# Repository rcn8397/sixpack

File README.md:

# sixpack
Six-Pack Cherry MX Macro Pad

# Layout
Six Switch MX Layout

# Plate & Case

 * Switch Type: MX {_t:3}
 * Stabilizer Type: Cherry + Costar {_s:1}
 * Case Type: Sandwich
 * USB Cutout: On
   * Location: 0 (default)
   * Width: 12
 * Mount Holes: 4, 3, 8
 * Edge Padding: On, 10,10,10,10 (W,N,E,S)
 * Plate Corners: On, 4
 * Custom Polygons: Off
 * Kerf: Off
 * Key Unit Size: Off
 * Line Color: Off
 * Line Weight: Off

## 3D Printing
The plate and case are also hosted on [prusaprinters.org](https://www.prusaprinters.org/prints/113097-sixpack)

### Openscad
Each layer can be generated/customized using openscads customizer. 

### Slicing
I use Cura to slice, but I suspect any slicer will work. 

* Nozzle: 0.4mm
* Layer Height: 0.2mm
* Supports: No

# QMK
## Setup
## Compiling
Compile the code using QMK

     qmk compile -kb handwired/sixpack  -km default
     
## Flashing
Flash the target (ProMicro), note you must hit the reset switch to enter bootloader.

     qmk flash -kb handwired/sixpack  -km default
     
### Linux Issues
On Ubuntu 18.04 I needed to stop the ModemManger service to communicate with ttyACM0 serial device. 

    sudo systemctl stop ModemManager.service
    sudo systemctl disable ModemManager.service
    
 ## Customization
 TODO

# Resources
 * https://www.youtube.com/watch?v=IKe_hrvYH1M
 * http://www.keyboard-layout-editor.com/
 * http://builder.swillkb.com/
 * https://wiki.ai03.com/books/pcb-design/chapter/pcb-designer-guide
 * https://matt3o.com/hand-wiring-a-custom-keyboard/

## QMK
 * https://docs.qmk.fm/#/
 * https://docs.qmk.fm/#/hand_wire
 * Sixpack firmware (QMK forked) https://github.com/rcn8397/qmk_firmware/tree/personal/nordeen%2Fsixpack
 * Work flow https://docs.qmk.fm/#/newbs_git_using_your_master_branch

### QMK Git Workflow/Setup
Add the forked repo as a remote

      git remote add myfork git@github.com:rcn8397/qmk_firmware.git
      
Next verify the forked repo was added

      git remote -v
      
Should look something like:

      myfork	git@github.com:rcn8397/qmk_firmware.git (fetch)
      myfork	git@github.com:rcn8397/qmk_firmware.git (push)
      origin	https://github.com/qmk/qmk_firmware.git (fetch)
      origin	https://github.com/qmk/qmk_firmware.git (push)
      
Next push the development branch to the fork and track it.

      git push -u myfork

## Promicro
 * https://deskthority.net/wiki/Arduino_Pro_Micro#Pinout
 * https://golem.hu/guide/pro-micro-upgrade/
 * https://learn.sparkfun.com/tutorials/pro-micro--fio-v3-hookup-guide/troubleshooting-and-faq#ts-reset

## Atmega32u4 Data sheet

 * http://ww1.microchip.com/downloads/en/devicedoc/atmel-7766-8-bit-avr-atmega16u4-32u4_datasheet.pdf

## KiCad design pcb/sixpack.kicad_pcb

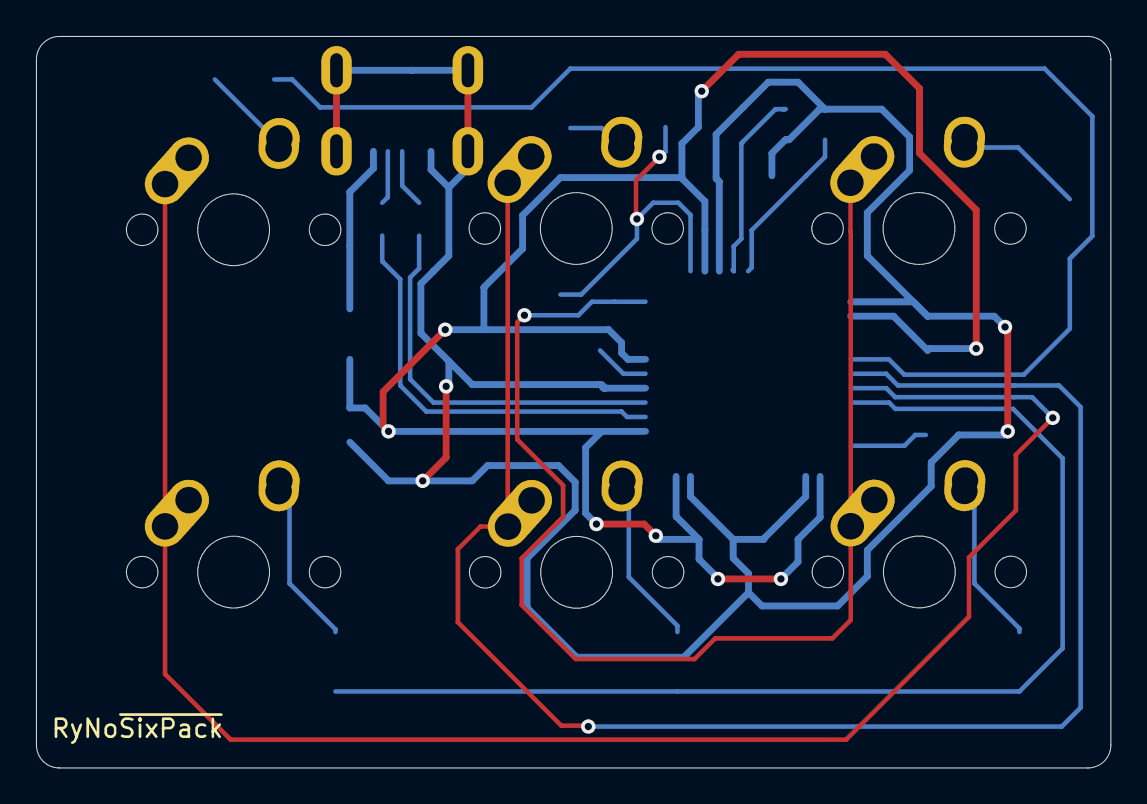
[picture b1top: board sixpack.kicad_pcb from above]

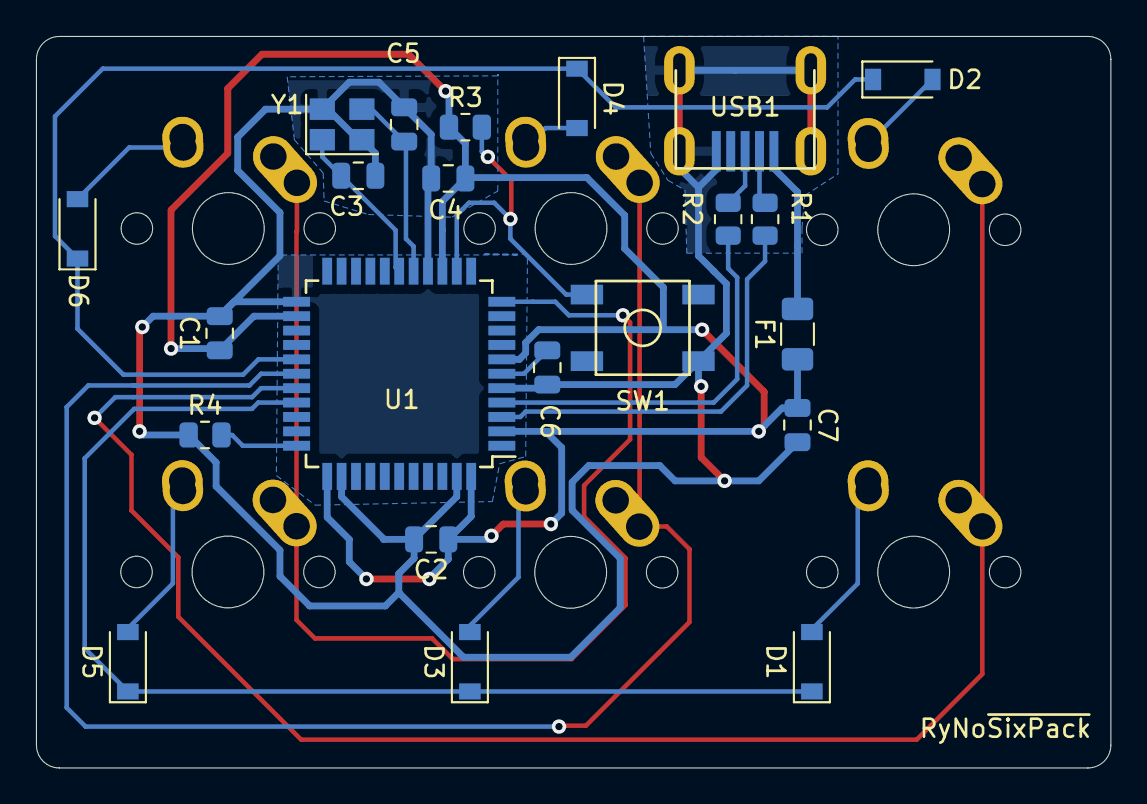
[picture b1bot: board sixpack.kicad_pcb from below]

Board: 2 copper layers, 59.7 x 40.6 mm, 28 parts (22 on the bottom side), 23 nets.

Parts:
C1, C2, C4: 0.1uF; C_0805_2012Metric
C3, C5: 22pF; C_0805_2012Metric
C6: 1uF; C_0805_2012Metric
C7: 10uF; C_0805_2012Metric
D1, D2, D3, D4, D5, D6: SOD-123; D_SOD-123
F1: 500mA; Fuse_1206_3216Metric
MX1, MX2, MX3, MX4, MX5, MX6: MX-NoLED; MX-1U-NoLED
R1, R2: 22; R_0805_2012Metric
R3, R4: 10k; R_0805_2012Metric
SW1: SW_Push; SKQG-1155865
U1: ATmega32U4-AU; TQFP-44_10x10mm_P0.8mm
USB1: Molex-0548190589
Y1: 16MHz; Crystal_SMD_3225-4Pin_3.2x2.5mm

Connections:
+5V: C1.1, C2.1, C4.1, C7.1, F1.1, R3.1, U1.2, U1.7, U1.14, U1.24, U1.34, U1.44
COL0: MX1.1, MX2.1, U1.29
COL1: MX3.1, MX4.1, U1.28
COL2: MX5.1, MX6.1, U1.11
D+: R2.2, USB1.3
D-: R1.2, USB1.4
GND: C1.2, C2.2, C3.2, C4.2, C5.2, C6.2, C7.2, R4.1, SW1.1, U1.5, U1.15, U1.23, U1.35, U1.43, USB1.1, USB1.6, Y1.2, Y1.4
unnamed: C3.1, U1.17, Y1.1
unnamed: C5.1, U1.16, Y1.3
unnamed: C6.1, U1.6
unnamed: D1.2, MX1.2
unnamed: D2.2, MX2.2
unnamed: D3.2, MX3.2
unnamed: D4.2, MX4.2
unnamed: D5.2, MX5.2
unnamed: D6.2, MX6.2
unnamed: R1.1, U1.3
unnamed: R2.1, U1.4
unnamed: R3.2, SW1.2, U1.13
unnamed: R4.2, U1.33
ROW0: D2.1, D4.1, D6.1, U1.27
ROW1: D1.1, D3.1, D5.1, U1.30
VCC: F1.2, USB1.5

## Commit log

2021-11-14 Adding keyboard layout
2021-11-14 added mechanical drawings
2021-11-14 SVG was not working, switched to dxf
2021-11-14 Fixed markdown syntax
2021-11-14 Changed to 1.5 height
2021-11-14 PCB design guide started
2021-11-14 Adding submodules for kicad libraries
2021-11-14 Documenting links used to develop the six pack
2021-11-14 Added MX/Alps and parts libraries
2021-11-14 Added short cuts guide
2021-11-15 Atmega32u4 schemtaic
2021-11-15 Added USB molex connection and six pack switch matrix.
2021-11-15 Assigned foot prints
2021-11-21 Decided on simple six pack layout
2021-11-24 finished routing
2021-11-24 moved 10uF to after the polyfuse
2021-11-25 connected usb ground pads and shrunk gnd plane
2021-11-25 Added Gerbers
2021-11-25 Moved labels
2021-11-28 Mech updates, adding promicro and rst button
2021-11-28 promicro fits
2021-11-29 bottom printed well and parts fit
2022-01-05 Update README.md
    QMK serial issues on Ubuntu 18.04
2022-01-05 Update README.md
    Improved outline and added resource links
2022-01-05 Update README.md
    More links
2022-01-17 Update README.md
    Added information on working with QMK.
2022-01-17 Update README.md
    Added information.
2022-01-23 Crafting neopixel tools
2022-01-23 hulled variant
2022-01-25 strip seems possible
2022-01-25 channel is now apart of the cube_iter
2022-01-25 jig created
2022-01-29 Trimming neo_pixel.scad
2022-01-29 Renamed neo_pixel to alitovo brand device
2022-01-29 renamed scad to led_layer
2022-02-01 reworking-led-layer
2022-02-01 starting to place ribbon strips
2022-02-05 working led layer
